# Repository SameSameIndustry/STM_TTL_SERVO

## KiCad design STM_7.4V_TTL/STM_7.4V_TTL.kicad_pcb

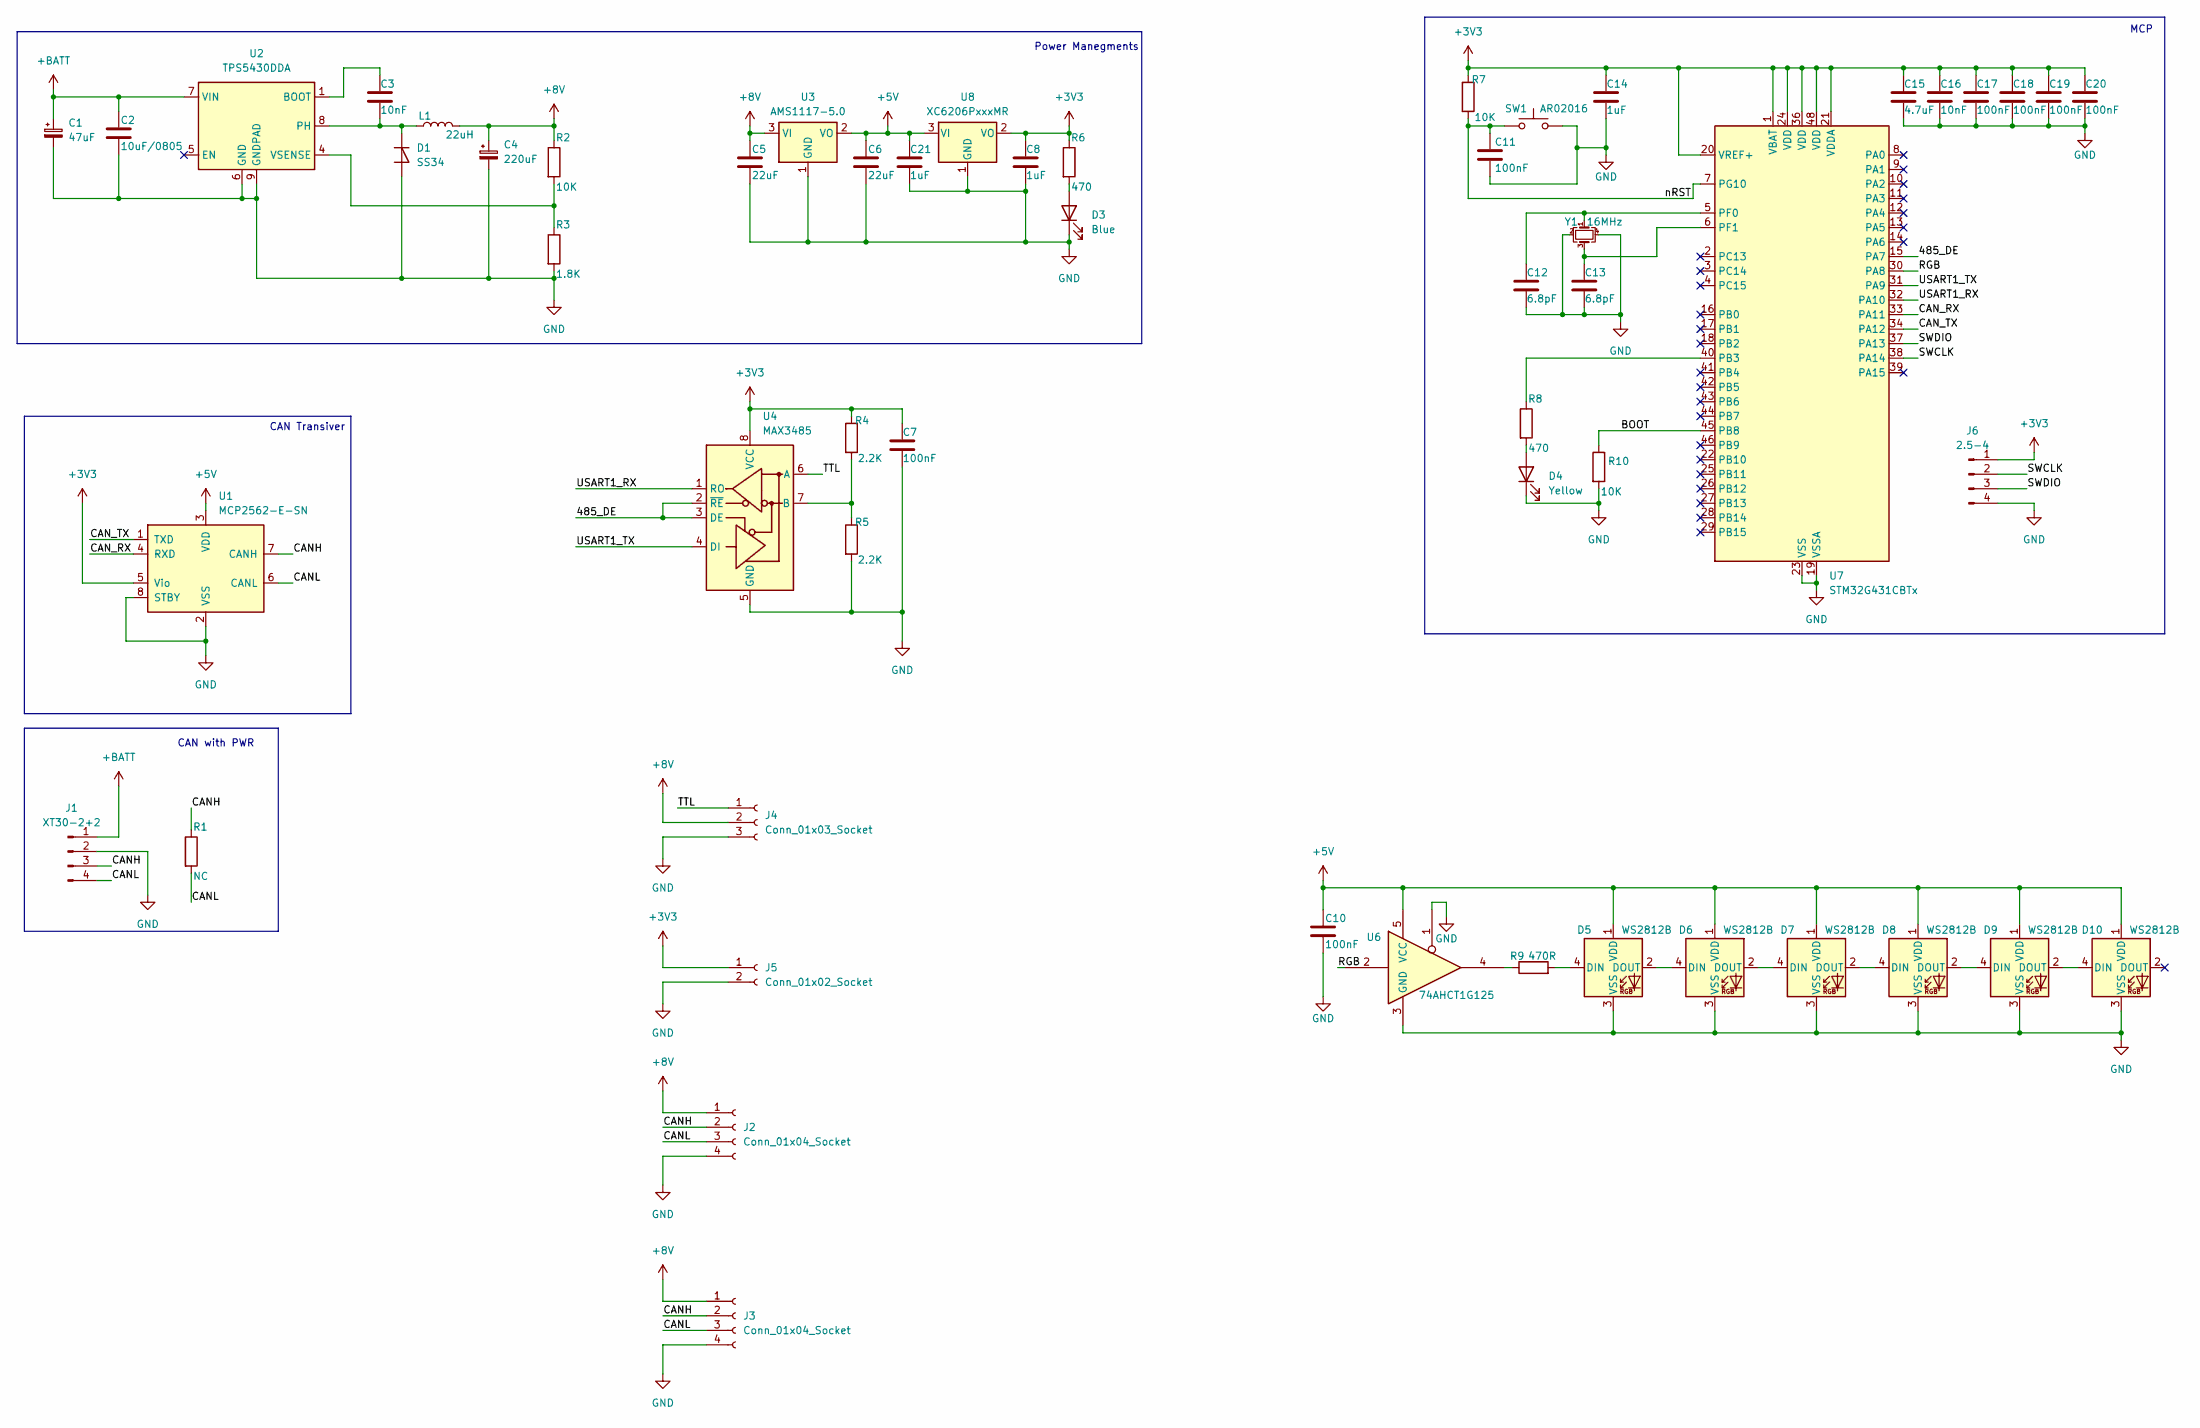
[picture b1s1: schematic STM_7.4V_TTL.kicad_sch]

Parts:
C1: 47uF; CP_Elec_6.3x5.4; LCSC C7461266
C2: 10uF/0805; C_0805_2012Metric; LCSC C440198
C3, C16: 10nF; C_0603_1608Metric_Pad1.08x0.95mm_HandSolder; LCSC C57112
C4: 220uF; CP_Elec_6.3x5.4; LCSC C22383796
C5, C6: 22uF; C_0603_1608Metric; LCSC C59461
C7, C10, C11, C17, C18, C19, C20: 100nF; C_0603_1608Metric_Pad1.08x0.95mm_HandSolder; LCSC C14663
C8, C14, C21: 1uF; C_0603_1608Metric_Pad1.08x0.95mm_HandSolder; LCSC C15849
C12, C13: 6.8pF; C_0603_1608Metric_Pad1.08x0.95mm_HandSolder; LCSC C1679
C15: 4.7uF; C_0603_1608Metric_Pad1.08x0.95mm_HandSolder; LCSC C19666
D1: SS34; D_SMA; LCSC C8678
D3: Blue; LED_0603_1608Metric_Pad1.05x0.95mm_HandSolder; LCSC C2288
D4: Yellow; LED_0603_1608Metric_Pad1.05x0.95mm_HandSolder; LCSC C2286
D5, D6, D7, D8, D9, D10: WS2812B; LED_WS2812B_PLCC4_5.0x5.0mm_P3.2mm
J1: XT30-2+2; CONN-TH_4P-XT30PW-M
J2, J3: Conn_01x04_Socket; JST_XH_B4B-XH-A_1x04_P2.50mm_Vertical
J4: Conn_01x03_Socket; JST_PH_S3B-PH-K_1x03_P2.00mm_Horizontal
J5: Conn_01x02_Socket; JST_PH_S2B-PH-K_1x02_P2.00mm_Horizontal
J6: 2.5-4; PinHeader_1x04_P2.54mm_Vertical
L1: 22uH; L_Bourns_SRP7028A_7.3x6.6mm; LCSC C22463831
R1: NC; R_0603_1608Metric_Pad0.98x0.95mm_HandSolder; LCSC C22787
R2, R7, R10: 10K; R_0603_1608Metric_Pad0.98x0.95mm_HandSolder; LCSC C95204
R3: 1.8K; R_0603_1608Metric_Pad0.98x0.95mm_HandSolder; LCSC C4177
R4, R5: 2.2K; R_0603_1608Metric_Pad0.98x0.95mm_HandSolder; LCSC C4190
R6, R8: 470; R_0603_1608Metric_Pad0.98x0.95mm_HandSolder; LCSC C23179
R9: 470R; R_0603_1608Metric_Pad0.98x0.95mm_HandSolder; LCSC C23179
SW1: AR02016; SW-SMD_L3.9-W3.0-P4.45; LCSC C720477
U1: MCP2562-E-SN; SOIC-8_3.9x4.9mm_P1.27mm; LCSC C53609
U2: TPS5430DDA; TI_SO-PowerPAD-8_ThermalVias; LCSC C9864
U3: AMS1117-5.0; SOT-223-3_TabPin2; LCSC C6187
U4: MAX3485; SOP-8_3.76x4.96mm_P1.27mm; LCSC C22447116
U6: 74AHCT1G125; SOT-23-5_HandSoldering; LCSC C7484
U7: STM32G431CBTx; LQFP-48_7x7mm_P0.5mm; LCSC C529355
U8: XC6206PxxxMR; SOT-23-3; LCSC C5446
Y1: 16MHz; Crystal_SMD_3225-4Pin_3.2x2.5mm; LCSC C13738

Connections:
+3V3: C7.1, C8.1, C14.1, C15.1, C16.1, C17.1, C18.1, C19.1, C20.1, J5.1, J6.1, R4.1, R6.1, R7.1, U1.5 (Vio), U4.8 (VCC), U7.1 (VBAT), U7.20 (VREF+), U7.21 (VDDA), U7.24 (VDD), U7.36 (VDD), U7.48 (VDD), U8.2 (VO)
+5V: C6.1, C10.1, C21.1, D5.1 (VDD), D6.1 (VDD), D7.1 (VDD), D8.1 (VDD), D9.1 (VDD), D10.1 (VDD), U1.3 (VDD), U3.2 (VO), U6.5 (VCC), U8.3 (VI)
+8V: C4.1, C5.1, J2.1, J3.1, J4.2, L1.2, R2.1, U3.3 (VI)
+BATT: C1.1, C2.1, J1.1, U2.7 (VIN)
/485_DE: U4.2 (~RE), U4.3 (DE), U7.15 (PA7)
/BOOT: R10.1, U7.45 (PB8)
/CANH: J1.3, J2.2, J3.2, R1.1, U1.7 (CANH)
/CANL: J1.4, J2.3, J3.3, R1.2, U1.6 (CANL)
/CAN_RX: U1.4 (RXD), U7.33 (PA11)
/CAN_TX: U1.1 (TXD), U7.34 (PA12)
/RGB: U6.2, U7.30 (PA8)
/SWCLK: J6.2, U7.38 (PA14)
/SWDIO: J6.3, U7.37 (PA13)
/TTL: J4.1, U4.6 (A)
/USART1_RX: U4.1 (RO), U7.32 (PA10)
/USART1_TX: U4.4 (DI), U7.31 (PA9)
/nRST: C11.1, R7.2, SW1.1, U7.7 (PG10)
GND: C1.2, C2.2, C4.2, C5.2, C6.2, C7.2, C8.2, C10.2, C11.2, C12.2, C13.2, C14.2, C15.2, C16.2, C17.2, C18.2, C19.2, C20.2, C21.2, D1.2 (A), D3.1 (K), D4.1 (K), D5.3 (VSS), D6.3 (VSS), D7.3 (VSS), D8.3 (VSS), D9.3 (VSS), D10.3 (VSS), J1.2, J2.4, J3.4, J4.3, J5.2, J6.4, R3.2, R5.2, R10.2, SW1.2, U1.2 (VSS), U1.8 (STBY), U2.6 (GND), U2.9 (GNDPAD), U3.1 (GND), U4.5 (GND), U6.1, U6.3 (GND), U7.19 (VSSA), U7.23 (VSS), U7.35 (VSS), U7.47 (VSS), U8.1 (GND), Y1.2, Y1.4
unnamed: C3.2, D1.1 (K), L1.1, U2.8 (PH)
unnamed: D3.2 (A), R6.2
unnamed: D4.2 (A), R8.2
unnamed: D5.4 (DIN), R9.2
unnamed: D5.2 (DOUT), D6.4 (DIN)
unnamed: D6.2 (DOUT), D7.4 (DIN)
unnamed: D7.2 (DOUT), D8.4 (DIN)
unnamed: D8.2 (DOUT), D9.4 (DIN)
unnamed: D9.2 (DOUT), D10.4 (DIN)
unnamed: R9.1, U6.4
unnamed: C3.1, U2.1 (BOOT)
unnamed: R2.2, R3.1, U2.4 (VSENSE)
unnamed: R4.2, R5.1, U4.7 (B)
unnamed: R8.1, U7.40 (PB3)
unnamed: C12.1, U7.5 (PF0), Y1.1
unnamed: C13.1, U7.6 (PF1), Y1.3

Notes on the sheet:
CAN with PWR
Power Manegments
MCP
CAN Transiver

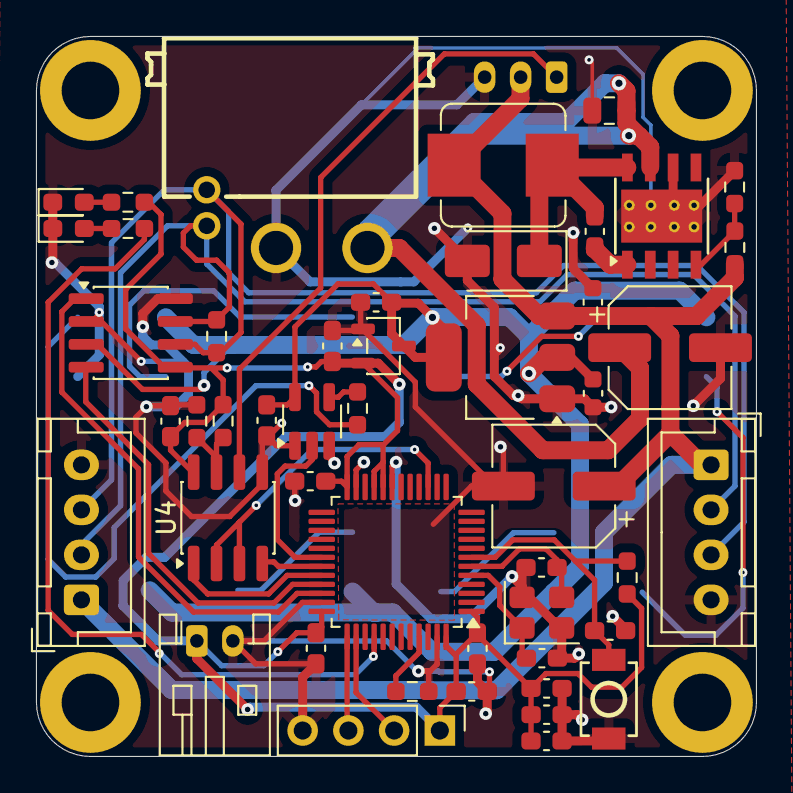
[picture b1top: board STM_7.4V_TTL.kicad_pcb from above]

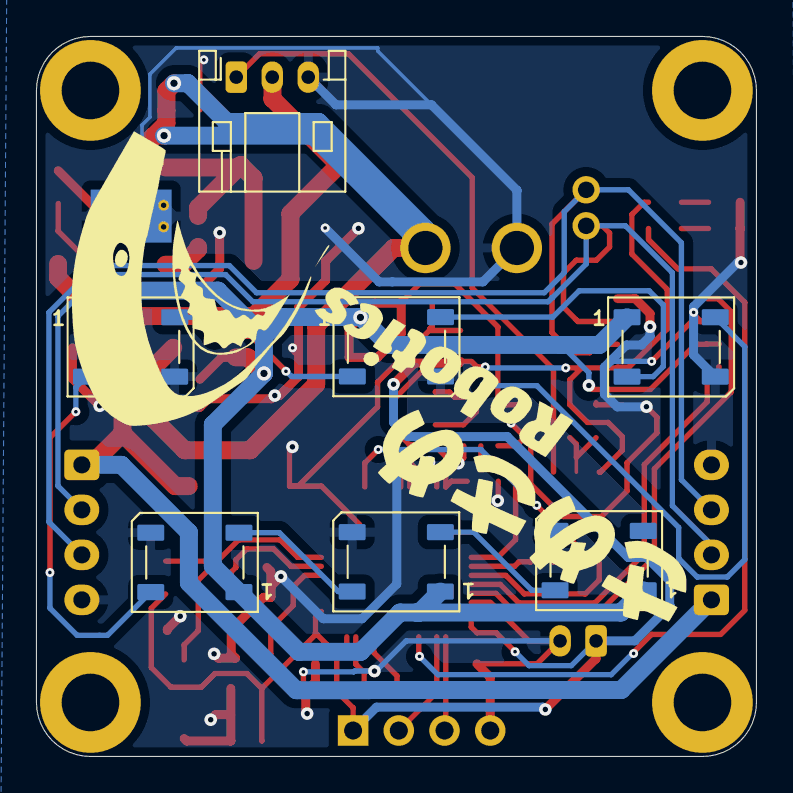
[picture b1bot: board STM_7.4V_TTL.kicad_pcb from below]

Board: 2 copper layers, 40.0 x 40.0 mm, 55 parts (7 on the bottom side), 34 nets.

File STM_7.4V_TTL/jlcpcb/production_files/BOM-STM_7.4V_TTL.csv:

Comment,Designator,Footprint,LCSC,Quantity
1.8K,R3,R_0603_1608Metric_Pad0.98x0.95mm_HandSolder,C4177,1
100nF,"C10,C11,C17,C18,C19,C20,C7",C_0603_1608Metric_Pad1.08x0.95mm_HandSolder,C14663,7
10K,"R10,R2,R7",R_0603_1608Metric_Pad0.98x0.95mm_HandSolder,C95204,3
10nF,"C16,C3",C_0603_1608Metric_Pad1.08x0.95mm_HandSolder,C57112,2
10uF/0805,C2,C_0805_2012Metric,C440198,1
16MHz,Y1,Crystal_SMD_3225-4Pin_3.2x2.5mm,C13738,1
1uF,"C14,C21,C8",C_0603_1608Metric_Pad1.08x0.95mm_HandSolder,C15849,3
2.2K,"R4,R5",R_0603_1608Metric_Pad0.98x0.95mm_HandSolder,C4190,2
220uF,C4,CP_Elec_6.3x5.4,C22383796,1
22uF,"C5,C6",C_0603_1608Metric,C59461,2
22uH,L1,L_Bourns_SRP7028A_7.3x6.6mm,C22463831,1
4.7uF,C15,C_0603_1608Metric_Pad1.08x0.95mm_HandSolder,C19666,1
470,"R6,R8",R_0603_1608Metric_Pad0.98x0.95mm_HandSolder,C23179,2
470R,R9,R_0603_1608Metric_Pad0.98x0.95mm_HandSolder,C23179,1
47uF,C1,CP_Elec_6.3x5.4,C7461266,1
6.8pF,"C12,C13",C_0603_1608Metric_Pad1.08x0.95mm_HandSolder,C1679,2
74AHCT1G125,U6,SOT-23-5_HandSoldering,C7484,1
AMS1117-5.0,U3,SOT-223-3_TabPin2,C6187,1
AR02016,SW1,SW-SMD_L3.9-W3.0-P4.45,C720477,1
Blue,D3,LED_0603_1608Metric_Pad1.05x0.95mm_HandSolder,C2288,1
MCP2562-E-SN,U1,SOIC-8_3.9x4.9mm_P1.27mm,C53609,1
NC,R1,R_0603_1608Metric_Pad0.98x0.95mm_HandSolder,C22787,1
SS34,D1,D_SMA,C8678,1
STM32G431CBTx,U7,LQFP-48_7x7mm_P0.5mm,C529355,1
TPS5430DDA,U2,TI_SO-PowerPAD-8_ThermalVias,C9864,1
XC6206PxxxMR,U8,SOT-23-3,C5446,1
Yellow,D4,LED_0603_1608Metric_Pad1.05x0.95mm_HandSolder,C2286,1
Conn_01x04_Socket,J2,JST_XH_B4B-XH-A_1x04_P2.50mm_Vertical,,1
Conn_01x02_Socket,J5,JST_PH_S2B-PH-K_1x02_P2.00mm_Horizontal,,1
MAX3485,U4,SOP-8_3.76x4.96mm_P1.27mm,,1
Conn_01x04_Socket,J3,JST_XH_B4B-XH-A_1x04_P2.50mm_Vertical,,1
XT30-2+2,J1,CONN-TH_4P-XT30PW-M,,1
2.5-4,J6,PinHeader_1x04_P2.54mm_Vertical,,1
WS2812B,D8,LED_WS2812B_PLCC4_5.0x5.0mm_P3.2mm,,1
WS2812B,D9,LED_WS2812B_PLCC4_5.0x5.0mm_P3.2mm,,1
WS2812B,D5,LED_WS2812B_PLCC4_5.0x5.0mm_P3.2mm,,1
WS2812B,D10,LED_WS2812B_PLCC4_5.0x5.0mm_P3.2mm,,1
Conn_01x03_Socket,J4,JST_PH_S3B-PH-K_1x03_P2.00mm_Horizontal,,1
WS2812B,D6,LED_WS2812B_PLCC4_5.0x5.0mm_P3.2mm,,1
WS2812B,D7,LED_WS2812B_PLCC4_5.0x5.0mm_P3.2mm,,1

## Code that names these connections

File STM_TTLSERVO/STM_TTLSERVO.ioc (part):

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Mcu.Name=STM32G431C(6-8-B)Tx
Mcu.Package=LQFP48
Mcu.UserName=STM32G431CBTx
PA10.Mode=Asynchronous
PA10.Signal=USART1_RX
PA11.Mode=FDCAN_Activate
PA11.Signal=FDCAN1_RX
PA12.Mode=FDCAN_Activate
PA12.Signal=FDCAN1_TX
PA7.Signal=GPIO_Output
PA8.Signal=S_TIM1_CH1
PA9.Mode=Asynchronous
PA9.Signal=USART1_TX
PB3.Signal=GPIO_Output
PF0-OSC_IN.Mode=HSE-External-Oscillator
PF0-OSC_IN.Signal=RCC_OSC_IN
PF1-OSC_OUT.Mode=HSE-External-Oscillator
PF1-OSC_OUT.Signal=RCC_OSC_OUT
RCC.HSE_VALUE=16000000
RCC.SYSCLKFreq_VALUE=80000000
RCC.SYSCLKSource=RCC_SYSCLKSOURCE_PLLCLK
board=custom
